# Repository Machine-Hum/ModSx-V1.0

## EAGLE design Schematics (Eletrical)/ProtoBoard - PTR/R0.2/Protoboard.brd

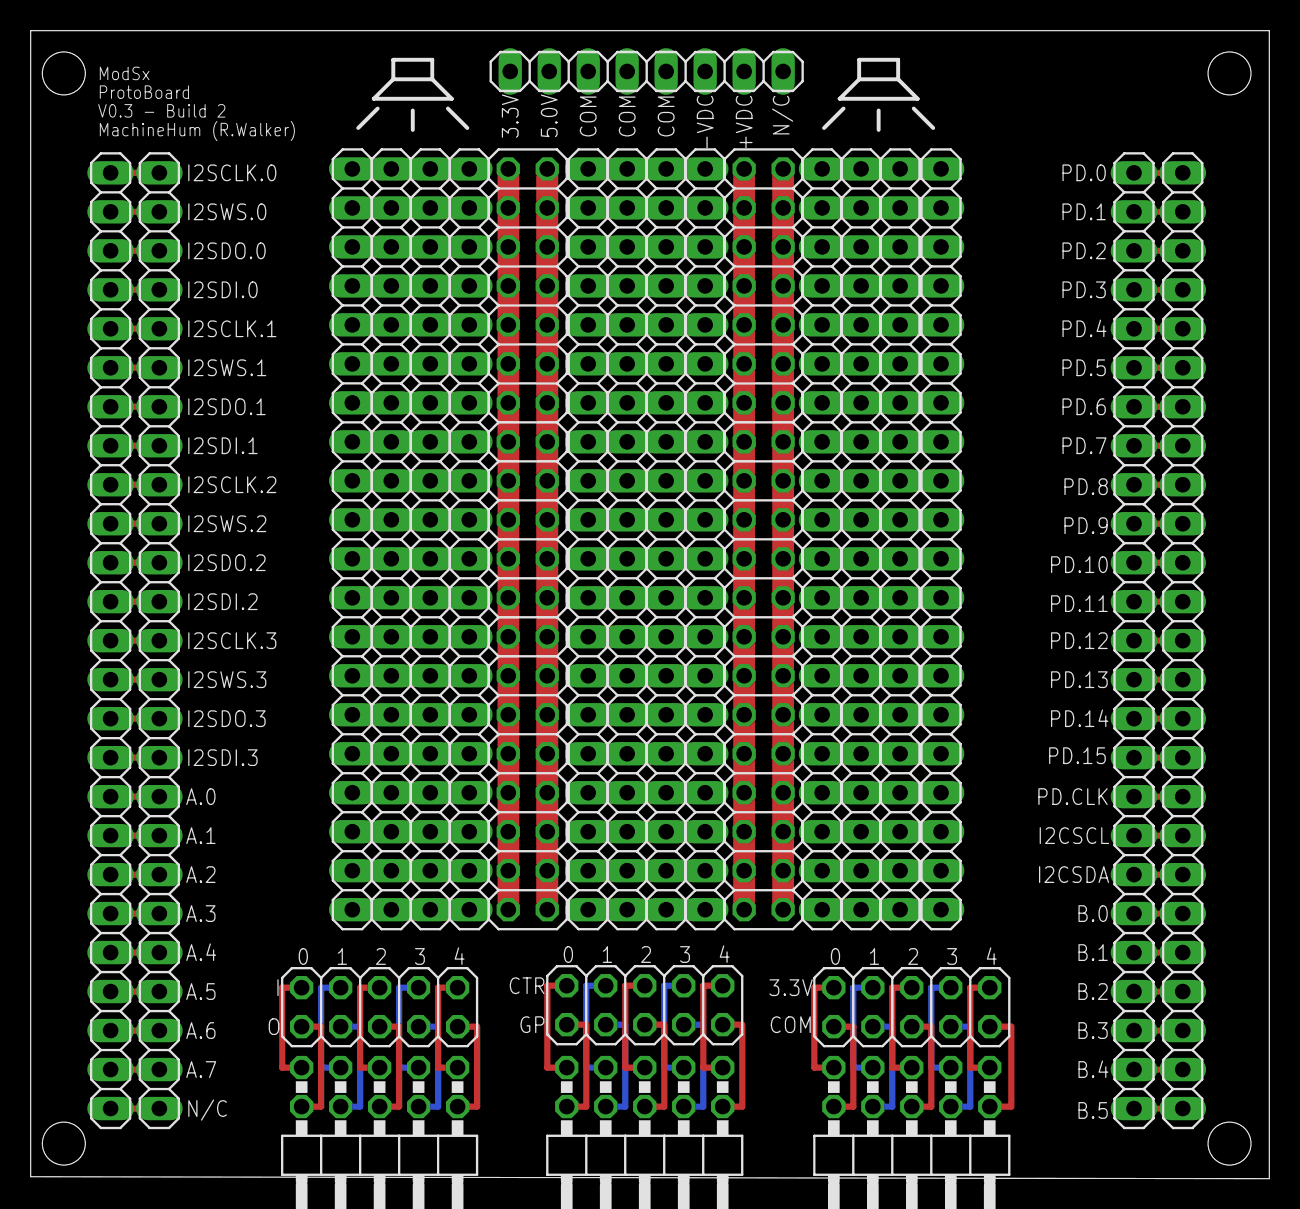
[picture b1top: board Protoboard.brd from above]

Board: 2 copper layers, 80.7 x 74.8 mm, 25 parts (0 on the bottom side), 145 nets.

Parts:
GYH, GYH1: 1X25
JP1, JP2: 1X25
JP3: 1X08
JP4, JP5, JP6: 2X05/90
JP7, JP8, JP9: 2X05
JP10, JP11, JP12, JP13, JP14, JP15, JP16, JP17, JP20, JP21, JP22, JP23: 1X20
JP18, JP19: 2X20

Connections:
unnamed: GYH.25, GYH1.1
unnamed: GYH.24, GYH1.2
unnamed: GYH.23, GYH1.3
unnamed: GYH.22, GYH1.4
unnamed: GYH.21, GYH1.5
unnamed: GYH.20, GYH1.6
unnamed: JP1.25, JP2.1
unnamed: JP1.24, JP2.2
unnamed: JP1.23, JP2.3
unnamed: JP1.22, JP2.4
unnamed: JP1.21, JP2.5
unnamed: JP1.19, JP2.7
unnamed: GYH.19, GYH1.7
unnamed: GYH.18, GYH1.8
unnamed: GYH.17, GYH1.9
unnamed: GYH.16, GYH1.10
unnamed: GYH.15, GYH1.11
unnamed: GYH.14, GYH1.12
unnamed: GYH.13, GYH1.13
unnamed: GYH.12, GYH1.14
unnamed: GYH.11, GYH1.15
unnamed: GYH.10, GYH1.16
unnamed: GYH.9, GYH1.17
unnamed: GYH.8, GYH1.18
unnamed: GYH.7, GYH1.19
unnamed: GYH.6, GYH1.20
unnamed: GYH.5, GYH1.21
unnamed: GYH.4, GYH1.22
unnamed: GYH.3, GYH1.23
unnamed: GYH.2, GYH1.24
unnamed: GYH.1, GYH1.25
unnamed: JP1.20, JP2.6
unnamed: JP1.18, JP2.8
unnamed: JP1.17, JP2.9
unnamed: JP1.16, JP2.10
unnamed: JP1.15, JP2.11
unnamed: JP1.14, JP2.12
unnamed: JP1.13, JP2.13
unnamed: JP1.12, JP2.14
unnamed: JP1.11, JP2.15
unnamed: JP1.10, JP2.16
unnamed: JP1.9, JP2.17
unnamed: JP1.8, JP2.18
unnamed: JP1.7, JP2.19
unnamed: JP1.6, JP2.20
unnamed: JP1.5, JP2.21
unnamed: JP1.4, JP2.22
unnamed: JP1.3, JP2.23
unnamed: JP1.2, JP2.24
unnamed: JP1.1, JP2.25
unnamed: JP4.1, JP7.1
unnamed: JP4.2, JP7.2
unnamed: JP4.3, JP7.3
unnamed: JP4.4, JP7.4
unnamed: JP4.5, JP7.5
unnamed: JP4.6, JP7.6
unnamed: JP4.7, JP7.7
unnamed: JP4.8, JP7.8
unnamed: JP4.9, JP7.9
unnamed: JP4.10, JP7.10
unnamed: JP5.1, JP8.1
unnamed: JP5.2, JP8.2
unnamed: JP5.3, JP8.3
unnamed: JP5.4, JP8.4
unnamed: JP5.5, JP8.5
unnamed: JP5.6, JP8.6
unnamed: JP5.7, JP8.7
unnamed: JP5.8, JP8.8
unnamed: JP5.9, JP8.9
unnamed: JP5.10, JP8.10
unnamed: JP6.1, JP9.1
unnamed: JP6.2, JP9.2
unnamed: JP6.3, JP9.3
unnamed: JP6.4, JP9.4
unnamed: JP6.5, JP9.5
unnamed: JP6.6, JP9.6
unnamed: JP6.7, JP9.7
unnamed: JP6.8, JP9.8
unnamed: JP6.9, JP9.9
unnamed: JP6.10, JP9.10
unnamed: JP10.1, JP11.20, JP12.1, JP13.1
unnamed: JP10.2, JP11.19, JP12.2, JP13.2
unnamed: JP10.3, JP11.18, JP12.3, JP13.3
unnamed: JP10.4, JP11.17, JP12.4, JP13.4
unnamed: JP10.5, JP11.16, JP12.5, JP13.5
unnamed: JP10.6, JP11.15, JP12.6, JP13.6
unnamed: JP10.7, JP11.14
unnamed: JP10.8, JP11.13, JP12.8, JP13.8
unnamed: JP10.9, JP11.12, JP12.9, JP13.9
unnamed: JP10.10, JP11.11, JP12.10, JP13.10
unnamed: JP10.11, JP11.10, JP12.11, JP13.11
unnamed: JP10.12, JP11.9, JP12.12, JP13.12
unnamed: JP10.13, JP11.8, JP12.13, JP13.13
unnamed: JP10.14, JP11.7, JP12.14, JP13.14
unnamed: JP10.15, JP11.6, JP12.15, JP13.15
unnamed: JP10.16, JP11.5, JP12.16, JP13.16
unnamed: JP10.17, JP11.4, JP12.17, JP13.17
unnamed: JP10.18, JP11.3, JP12.18, JP13.18
unnamed: JP10.19, JP11.2, JP12.19, JP13.19
unnamed: JP12.7, JP13.7
unnamed: JP14.1, JP15.20, JP16.1, JP17.1
unnamed: JP10.20, JP11.1, JP12.20, JP13.20
unnamed: JP14.2, JP15.19, JP16.2, JP17.2
unnamed: JP14.3, JP15.18, JP16.3, JP17.3
unnamed: JP14.4, JP15.17, JP16.4, JP17.4
unnamed: JP14.5, JP15.16, JP16.5, JP17.5
unnamed: JP14.6, JP15.15, JP16.6, JP17.6
unnamed: JP14.7, JP15.14, JP16.7, JP17.7
unnamed: JP14.8, JP15.13, JP16.8, JP17.8
unnamed: JP14.9, JP15.12, JP16.9, JP17.9
unnamed: JP14.10, JP15.11, JP16.10, JP17.10
unnamed: JP14.11, JP15.10, JP16.11, JP17.11
unnamed: JP14.12, JP15.9, JP16.12, JP17.12
unnamed: JP14.13, JP15.8, JP16.13, JP17.13
unnamed: JP14.14, JP15.7, JP16.14, JP17.14
unnamed: JP14.15, JP15.6, JP16.15, JP17.15
unnamed: JP14.16, JP15.5, JP16.16, JP17.16
unnamed: JP14.17, JP15.4, JP16.17, JP17.17
unnamed: JP14.18, JP15.3, JP16.18, JP17.18
unnamed: JP14.19, JP15.2, JP16.19, JP17.19
unnamed: JP14.20, JP15.1, JP16.20, JP17.20
unnamed: JP18.1, JP18.3, JP18.5, JP18.7, JP18.9, JP18.11, JP18.13, JP18.15, JP18.17, JP18.19, JP18.21, JP18.23, JP18.25, JP18.27, JP18.29, JP18.31, JP18.33, JP18.35, JP18.37, JP18.39
unnamed: JP18.2, JP18.4, JP18.6, JP18.8, JP18.10, JP18.12, JP18.14, JP18.16, JP18.18, JP18.20, JP18.22, JP18.24, JP18.26, JP18.28, JP18.30, JP18.32, JP18.34, JP18.36, JP18.38, JP18.40
unnamed: JP19.1, JP19.3, JP19.5, JP19.7, JP19.9, JP19.11, JP19.13, JP19.15, JP19.17, JP19.19, JP19.21, JP19.23, JP19.25, JP19.27, JP19.29, JP19.31, JP19.33, JP19.35, JP19.37, JP19.39
unnamed: JP19.2, JP19.4, JP19.6, JP19.8, JP19.10, JP19.12, JP19.14, JP19.16, JP19.18, JP19.20, JP19.22, JP19.24, JP19.26, JP19.28, JP19.30, JP19.32, JP19.34, JP19.36, JP19.38, JP19.40
unnamed: JP20.1, JP21.20, JP22.1, JP23.1
unnamed: JP20.2, JP21.19, JP22.2, JP23.2
unnamed: JP20.3, JP21.18, JP22.3, JP23.3
unnamed: JP20.4, JP21.17, JP22.4, JP23.4
unnamed: JP20.5, JP21.16, JP22.5, JP23.5
unnamed: JP20.6, JP21.15, JP22.6, JP23.6
unnamed: JP20.7, JP21.14, JP22.7, JP23.7
unnamed: JP20.8, JP21.13, JP22.8, JP23.8
unnamed: JP20.9, JP21.12, JP22.9, JP23.9
unnamed: JP20.10, JP21.11, JP22.10, JP23.10
unnamed: JP20.11, JP21.10, JP22.11, JP23.11
unnamed: JP20.12, JP21.9, JP22.12, JP23.12
unnamed: JP20.13, JP21.8, JP22.13, JP23.13
unnamed: JP20.14, JP21.7, JP22.14, JP23.14
unnamed: JP20.15, JP21.6, JP22.15, JP23.15
unnamed: JP20.16, JP21.5, JP22.16, JP23.16
unnamed: JP20.17, JP21.4, JP22.17, JP23.17
unnamed: JP20.18, JP21.3, JP22.18, JP23.18
unnamed: JP20.19, JP21.2, JP22.19, JP23.19
unnamed: JP20.20, JP21.1, JP22.20, JP23.20
